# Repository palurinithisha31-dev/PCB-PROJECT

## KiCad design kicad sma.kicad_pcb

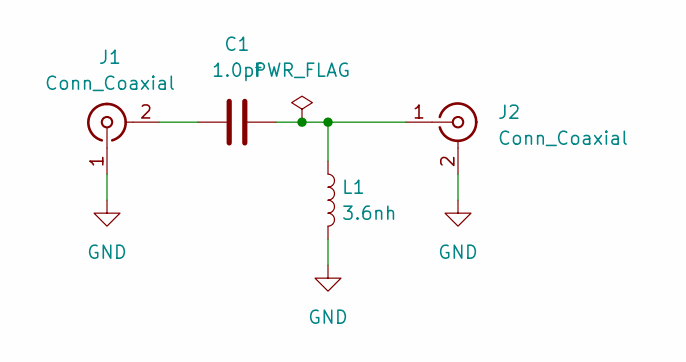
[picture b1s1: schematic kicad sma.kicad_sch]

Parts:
C1: 1.0pf; CP_Axial_L10.0mm_D4.5mm_P15.00mm_Horizontal
J1, J2: Conn_Coaxial; SMA_Amphenol_132134-10_Vertical
L1: 3.6nh; L_Axial_L5.3mm_D2.2mm_P2.54mm_Vertical_Vishay_IM-1

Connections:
GND: J1.1 (In), J2.2 (Ext), L1.2
unnamed: C1.1, J1.2 (Ext)
unnamed: C1.2, J2.1 (In), L1.1

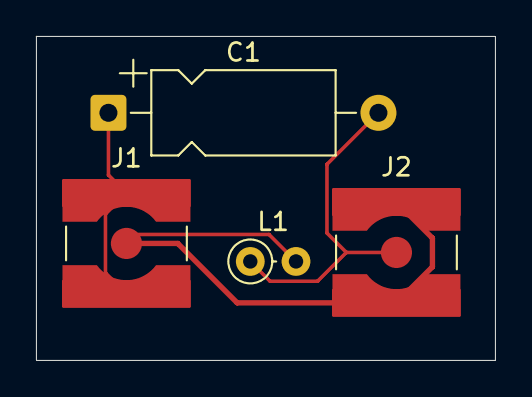
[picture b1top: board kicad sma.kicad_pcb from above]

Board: 2 copper layers, 25.5 x 18.0 mm, 4 parts (0 on the bottom side), 3 nets.
